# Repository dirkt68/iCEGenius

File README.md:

# iCEGenius (WIP)

**STILL A WORK IN PROGRESS, DONT USE UNTIL THIS MESSAGE IS GONE**

A low cost, low power, minimally sized FPGA development board based on the iCE40LP384 FPGA.

## Table of Contents
- [iCEGenius (WIP)](#icegenius-wip-1)
  - [Table of Contents](#table-of-contents-1)
  - [Project Goal](#project-goal-1)
  - [Setup](#setup-1)
  - [Directory Structure](#directory-structure-1)
  - [Support](#support-1)
  - [Wishlist](#wishlist-1)
  - [Author Information](#author-information-1)

## Project Goal

Hobbyist grade FPGAs are in relatively short supply and are typically complicated for new users to dive into. Even the cheapest ones still range in the 30-40 dollar territory, which can be prohibitively expensive for institutions or groups without a large budget. To fill this void, the iCEGenius has been developed as an educational tool for use in learning introductory to intermediate Verilog on a real hardware target.

{INSERT 3D RENDER PIC}

The iCEGenius has been designed with cost and ease of use in mind. The total bill of materials is only $13.00 USD, which is cheaper than any of the common development FPGAs on the market. The board is designed to fit comfortably into a standard breadboard with space for multiple connections on either pin. With 16 accessible GPIOs, the board is very expandable for anything from simple blinky LEDs to more complex designs.

{INSERT PIC OF BOARD ON BREADBOARD}

The toolchain is a Visual Studio Code extension which supports one click simulations using iverilog and gtkwave and full synthesis using yosys and nextpnr. The [oss-cad-suite](https://github.com/YosysHQ/oss-cad-suite-build) was used as the main backend as all the necessary programs were included by default. A custom program designed to flash the bitstream using the MCP2210 USB-SPI interface is used as the uploader. All of the complicated command line work is handled by the extension, allowing for a low barrier to entry to those who want to learn.

The PCB was developed in Kicad 7.0 and the extension supports Visual Studio Code 1.77.0 and greater.

**IMPORTANT: ONLY WINDOWS IS SUPPORTED AT THIS TIME**

## Setup

1. Grab the latest binary of oss-cad-suite from https://github.com/YosysHQ/oss-cad-suite-build and extract to `C:/oss-cad-suite`.
2. Install the latest binary of the iCEGenius Programmer from the [`Releases`](https://github.com/dirkt68/iCEGenius/releases/) Tab.
3. Install [Visual Studio Code](https://code.visualstudio.com) and install the iCEGenius (ADD HYPERLINK TO EXTENSION) extension.
4. Write some Verilog and upload to your board!

## Directory Structure

- board (where anything related to PCB lives)
  - bom (bill of materials for v2 and v1)
  - iCEGenius-backups (kicad automatic backups)
  - information (datasheets and a pinout guide for the FPGA)
  - jlcpcb (where the production files are autogenerated (gerbers, cpl, etc.))
  - pdf (easy reference to schematic and layout)
  - sims (electronic simulations)
  - kicad board files (open in kicad)
- extension (where the vscode extension lives)
  - standard Visual Studio Code layout for an extension
- programmer (where the program to program the board lives)
  - etc (user guides, etc.)
  - includes (*.h files)
  - libs (*.lib files)
  - src (main code)

## Support
- Any suggestions are welcome! I will not be super active all the time, but I'd like to maintain the project as much as I can.

## Wishlist
- add linux and mac support
- host a prebuilt board somewhere where people can buy (where?)

## Author Information
- Made by Dirk Thieme for use in ECE 2372 for the Capstone Project Lab at Texas Tech University. Advised by Derek A. Johnston.

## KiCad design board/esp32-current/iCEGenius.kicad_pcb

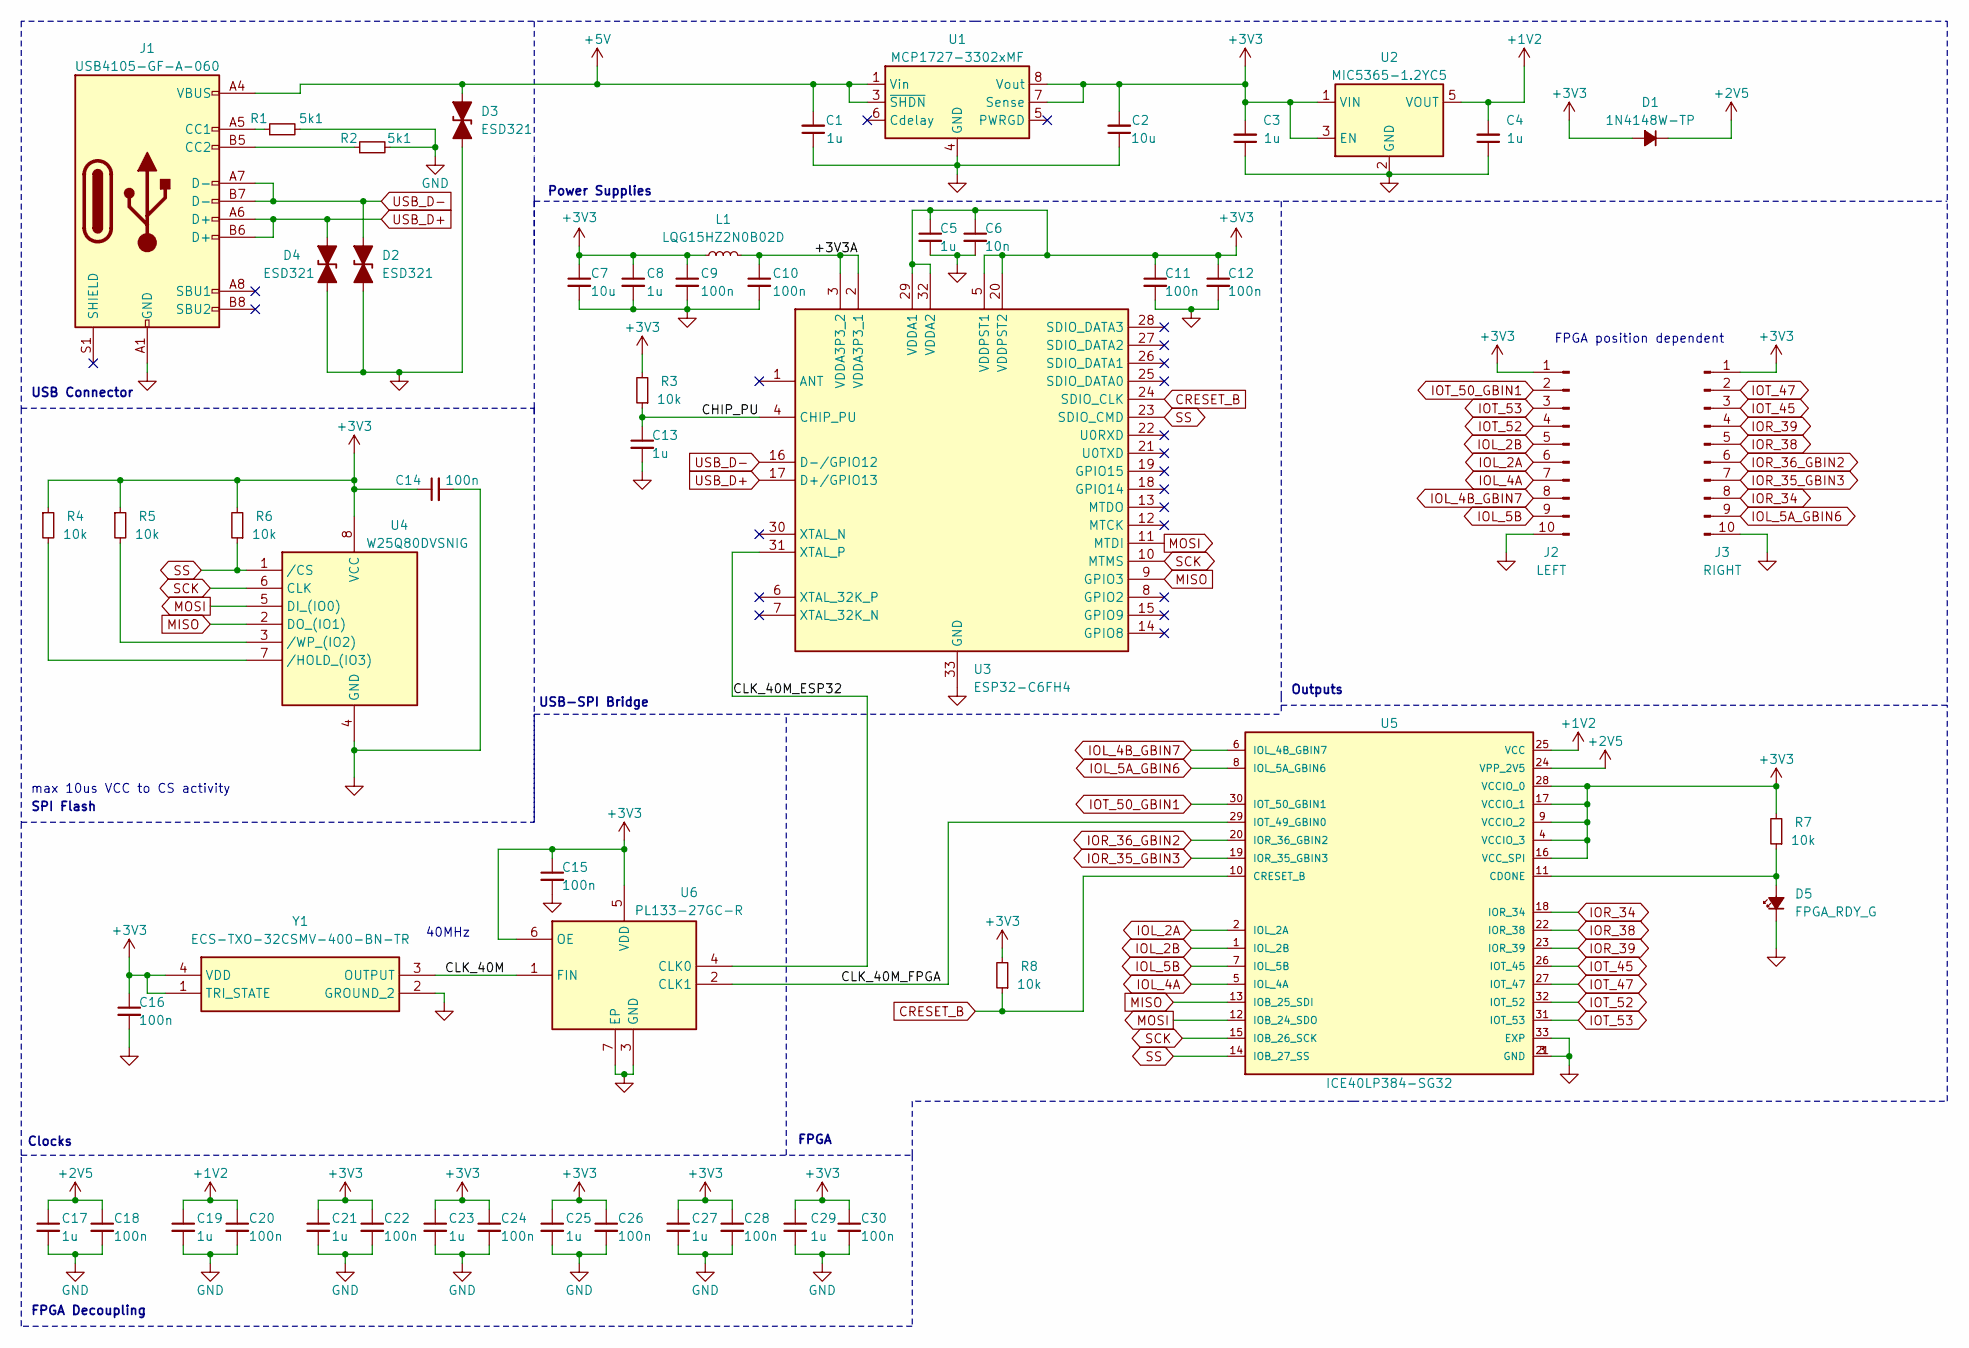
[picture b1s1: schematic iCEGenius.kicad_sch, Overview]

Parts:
C1, C3, C4, C5, C8, C13, C17, C19, C21, C23, C25, C27, C29: 1u; C_0402_1005Metric
C2, C7: 10u; C_0402_1005Metric
C6: 10n; C_0201_0603Metric
C9, C10, C11, C12, C14, C15, C16, C18, C20, C22, C24, C26, C28, C30: 100n; C_0201_0603Metric
D1: 1N4148W-TP; D_SOD-123
D2, D3, D4: ESD321; D_0402_1005Metric_TVS
D5: FPGA_RDY_G; LED_0603_1608Metric
J1: USB4105-GF-A-060; USB_C_Receptacle_GCT_USB4105-xx-A_16P_TopMnt_Horizontal
J2: LEFT; PinSocket_1x10_P2.54mm_Vertical
J3: RIGHT; PinSocket_1x10_P2.54mm_Vertical
L1: LQG15HZ2N0B02D; L_0402_1005Metric
R1, R2: 5k1; R_0402_1005Metric
R3, R4, R5, R6, R7, R8: 10k; R_0402_1005Metric
U1: MCP1727-3302xMF; DFN-8-1EP_3x3mm_P0.65mm_EP1.55x2.4mm
U2: MIC5365-1.2YC5; SOT-353_SC-70-5
U3: ESP32-C6FH4; QFN50P500X500X90-33N; Mouser Part Number 356-ESP32-C6FH4
U4: W25Q80DVSNIG; SOIC127P600X175-8N; Mouser Part Number 454-W25Q80DVSNIG
U5: ICE40LP384-SG32; HVQFN-32-1EP_5x5mm_P0.5mm_EP3.1x3.1mm
U6: PL133-27GC-R; SON40P200X130X60-7N-D; Mouser Part Number 998-PL133-27GC-R
Y1: ECS-TXO-32CSMV-400-BN-TR; ECSTXO32CSMV400BNTR; Mouser Part Number 520-TXO32CSMV400BNTR

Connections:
+1V2: C4.2, C19.1, C20.1, U2.5 (VOUT), U5.25 (VCC)
+2V5: C17.1, C18.1, D1.1 (K), U5.24 (VPP_2V5)
+3V3: C2.2, C3.2, C5.1, C6.1, C7.1, C8.1, C9.1, C11.1, C12.1, C14.1, C15.1, C16.1, C21.1, C22.1, C23.1, C24.1, C25.1, C26.1, C27.1, C28.1, C29.1, C30.1, D1.2 (A), J2.1, J3.1, L1.1, R3.2, R4.1, R5.1, R6.2, R7.2, R8.2, U1.7 (Sense), U1.8 (Vout), U2.1 (VIN), U2.3 (EN), U3.5 (VDDPST1), U3.20 (VDDPST2), U3.29 (VDDA1), U3.32 (VDDA2), U4.8 (VCC), U5.4 (VCCIO_3), U5.9 (VCCIO_2), U5.16 (VCC_SPI), U5.17 (VCCIO_1), U5.28 (VCCIO_0), U6.5 (VDD), U6.6 (OE), Y1.1 (TRI_STATE), Y1.4 (VDD)
+5V: C1.2, D3.2 (A2), J1.A4 (VBUS), J1.A9 (VBUS), J1.B4 (VBUS), J1.B9 (VBUS), U1.1 (Vin), U1.2 (Vin), U1.3 (~SHDN)
/+3V3A: C10.1, L1.2, U3.2 (VDDA3P3_1), U3.3 (VDDA3P3_2)
/CHIP_PU: C13.1, R3.1, U3.4 (CHIP_PU)
/CLK_40M: U6.1 (FIN), Y1.3 (OUTPUT)
/CLK_40M_ESP32: U3.31 (XTAL_P), U6.4 (CLK0)
/CLK_40M_FPGA: U5.29 (IOT_49_GBIN0), U6.2 (CLK1)
CRESET_B: R8.1, U3.24 (SDIO_CLK), U5.10 (CRESET_B)
GND: C1.1, C2.1, C3.1, C4.1, C5.2, C6.2, C7.2, C8.2, C9.2, C10.2, C11.2, C12.2, C13.2, C14.2, C15.2, C16.2, C17.2, C18.2, C19.2, C20.2, C21.2, C22.2, C23.2, C24.2, C25.2, C26.2, C27.2, C28.2, C29.2, C30.2, D2.1 (A1), D3.1 (A1), D4.1 (A1), D5.1 (K), J1.A1 (GND), J1.A12 (GND), J1.B1 (GND), J1.B12 (GND), J2.10, J3.10, R1.2, R2.2, U1.4 (GND), U1.9 (GND), U2.2 (GND), U3.33 (GND), U4.4 (GND), U5.3 (GND), U5.21 (GND), U5.33 (EXP), U6.3 (GND), U6.7 (EP), Y1.2 (GROUND_2)
IOL_2A: J2.6, U5.2 (IOL_2A)
IOL_2B: J2.5, U5.1 (IOL_2B)
IOL_4A: J2.7, U5.5 (IOL_4A)
IOL_4B_GBIN7: J2.8, U5.6 (IOL_4B_GBIN7)
IOL_5A_GBIN6: J3.9, U5.8 (IOL_5A_GBIN6)
IOL_5B: J2.9, U5.7 (IOL_5B)
IOR_34: J3.8, U5.18 (IOR_34)
IOR_35_GBIN3: J3.7, U5.19 (IOR_35_GBIN3)
IOR_36_GBIN2: J3.6, U5.20 (IOR_36_GBIN2)
IOR_38: J3.5, U5.22 (IOR_38)
IOR_39: J3.4, U5.23 (IOR_39)
IOT_45: J3.3, U5.26 (IOT_45)
IOT_47: J3.2, U5.27 (IOT_47)
IOT_50_GBIN1: J2.2, U5.30 (IOT_50_GBIN1)
IOT_52: J2.4, U5.32 (IOT_52)
IOT_53: J2.3, U5.31 (IOT_53)
MISO: U3.9 (GPIO3), U4.2 (DO_(IO1)), U5.13 (IOB_25_SDI)
MOSI: U3.11 (MTDI), U4.5 (DI_(IO0)), U5.12 (IOB_24_SDO)
unnamed: D5.2 (A), R7.1, U5.11 (CDONE)
unnamed: J1.A5 (CC1), R1.1
unnamed: J1.B5 (CC2), R2.1
unnamed: R4.2, U4.7 (/HOLD_(IO3))
unnamed: R5.2, U4.3 (/WP_(IO2))
SCK: U3.10 (MTMS), U4.6 (CLK), U5.15 (IOB_26_SCK)
SS: R6.1, U3.23 (SDIO_CMD), U4.1 (/CS), U5.14 (IOB_27_SS)
USB_D+: D4.2 (A2), J1.A6 (D+), J1.B6 (D+), U3.17 (D+/GPIO13)
USB_D-: D2.2 (A2), J1.A7 (D-), J1.B7 (D-), U3.16 (D-/GPIO12)

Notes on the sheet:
USB-SPI Bridge
SPI Flash
40MHz
Power Supplies
Outputs
max 10us VCC to CS activity
FPGA
Clocks
FPGA position dependent
USB Connector
FPGA Decoupling

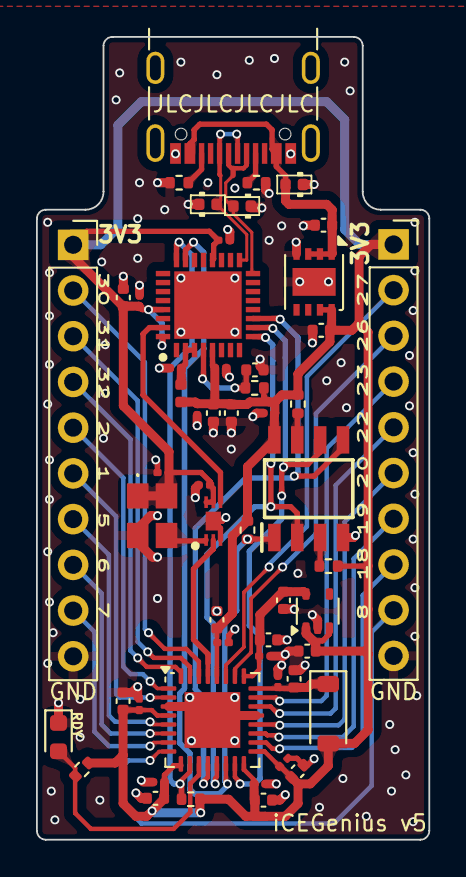
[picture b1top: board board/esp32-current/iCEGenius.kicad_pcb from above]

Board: 4 copper layers, 21.8 x 44.6 mm, 54 parts (0 on the bottom side), 38 nets.

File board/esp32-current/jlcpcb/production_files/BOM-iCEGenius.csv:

Comment,Designator,Footprint,LCSC
1u,C1,C_0402_1005Metric,
100n,C10,C_0201_0603Metric,
100n,C11,C_0201_0603Metric,
100n,C12,C_0201_0603Metric,
1u,C13,C_0402_1005Metric,
100n,C14,C_0201_0603Metric,
100n,C15,C_0201_0603Metric,
100n,C16,C_0201_0603Metric,
1u,C17,C_0402_1005Metric,
100n,C18,C_0201_0603Metric,
1u,C19,C_0402_1005Metric,
10u,C2,C_0402_1005Metric,
100n,C20,C_0201_0603Metric,
1u,C21,C_0402_1005Metric,
100n,C22,C_0201_0603Metric,
1u,C23,C_0402_1005Metric,
100n,C24,C_0201_0603Metric,
1u,C25,C_0402_1005Metric,
100n,C26,C_0201_0603Metric,
1u,C27,C_0402_1005Metric,
100n,C28,C_0201_0603Metric,
1u,C29,C_0402_1005Metric,
1u,C3,C_0402_1005Metric,
100n,C30,C_0201_0603Metric,
1u,C4,C_0402_1005Metric,
1u,C5,C_0402_1005Metric,
10n,C6,C_0201_0603Metric,
10u,C7,C_0402_1005Metric,
1u,C8,C_0402_1005Metric,
100n,C9,C_0201_0603Metric,
1N4148W-TP,D1,D_SOD-123,
ESD321,D2,D_0402_1005Metric_TVS,
ESD321,D3,D_0402_1005Metric_TVS,
ESD321,D4,D_0402_1005Metric_TVS,
FPGA_DONE_G,D5,LED_0603_1608Metric,
USB4105-GF-A-060,J1,USB_C_Receptacle_GCT_USB4105-xx-A_16P_TopMnt_Horizontal,
LEFT,J2,PinSocket_1x10_P2.54mm_Vertical,
RIGHT,J3,PinSocket_1x10_P2.54mm_Vertical,
LQG15HZ2N0B02D,L1,L_0402_1005Metric,
5k1,R1,R_0402_1005Metric,
5k1,R2,R_0402_1005Metric,
10k,R3,R_0402_1005Metric,
10k,R4,R_0402_1005Metric,
10k,R5,R_0402_1005Metric,
10k,R6,R_0402_1005Metric,
10k,R7,R_0402_1005Metric,
10k,R8,R_0402_1005Metric,
MCP1727-3302xMF,U1,DFN-8-1EP_3x3mm_P0.65mm_EP1.55x2.4mm,
MIC5365-1.2YC5,U2,SOT-353_SC-70-5,
ESP32-C6FH4,U3,QFN50P500X500X90-33N,
W25Q80DVSNIG,U4,SOIC127P600X175-8N,
ICE40LP384-SG32,U5,HVQFN-32-1EP_5x5mm_P0.5mm_EP3.1x3.1mm,
PL133-27GC-R,U6,SON40P200X130X60-7N-D,
ECS-TXO-32CSMV-400-BN-TR,Y1,ECSTXO32CSMV400BNTR,

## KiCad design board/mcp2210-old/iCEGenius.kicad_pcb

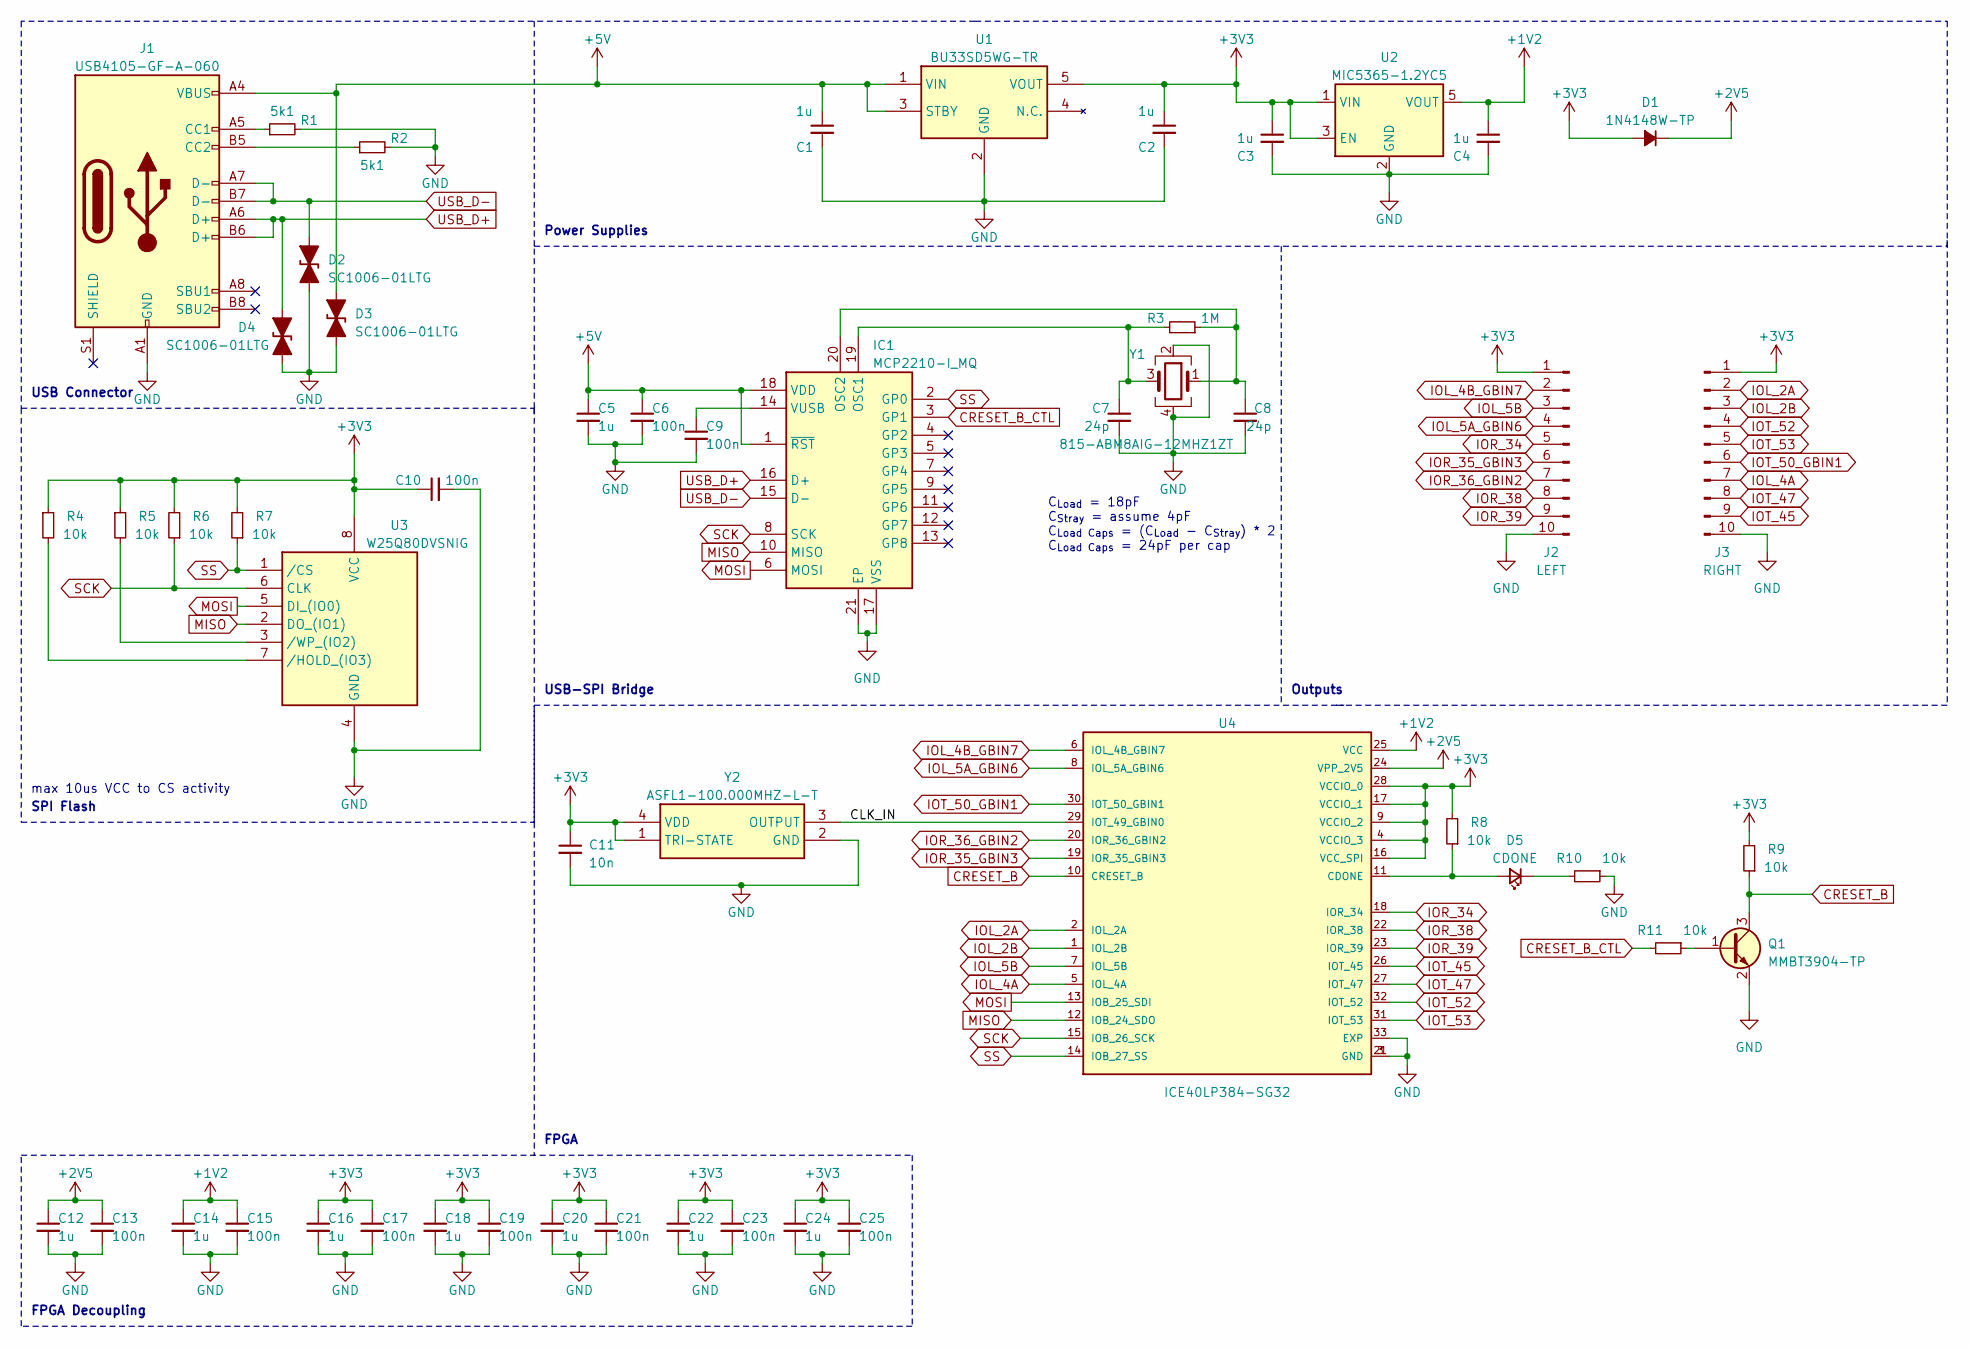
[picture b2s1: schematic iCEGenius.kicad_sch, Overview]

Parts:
C1, C2, C3, C4, C5, C12, C14, C16, C18, C20, C22, C24: 1u; C_0402_1005Metric
C6, C9, C10, C13, C15, C17, C19, C21, C23, C25: 100n; C_0201_0603Metric
C7, C8: 24p; C_0201_0603Metric
C11: 10n; C_0201_0603Metric
D1: 1N4148W-TP; D_SOD-123
D2, D3, D4: SC1006-01LTG; D_SOD-523_TVS
D5: CDONE; D_0603_1608Metric
IC1: MCP2210-I_MQ; QFN65P500X500X100-21N-D; Mouser Part Number 579-MCP2210IMQ
J1: USB4105-GF-A-060; USB_C_Receptacle_GCT_USB4105-xx-A_16P_TopMnt_Horizontal
J2: LEFT; PinSocket_1x10_P2.54mm_Vertical
J3: RIGHT; PinSocket_1x10_P2.54mm_Vertical
Q1: MMBT3904-TP; SOT-23
R1, R2: 5k1; R_0402_1005Metric
R3: 1M; R_0402_1005Metric
R4, R5, R6, R7, R8, R9, R10, R11: 10k; R_0402_1005Metric
U1: BU33SD5WG-TR; SOT95P280X125-5N; Mouser Part Number 755-BU33SD5WG-TR
U2: MIC5365-1.2YC5; SOT-353_SC-70-5
U3: W25Q80DVSNIG; SOIC127P600X175-8N; Mouser Part Number 454-W25Q80DVSNIG
U4: ICE40LP384-SG32; HVQFN-32-1EP_5x5mm_P0.5mm_EP3.1x3.1mm
Y1: 815-ABM8AIG-12MHZ1ZT; ABM8AIG25000MHZ122ZT3
Y2: ASFL1-100.000MHZ-L-T; ASFL1; Manufacturer_Part_Number ASFL1-100.000MHZ-L-T

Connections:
+1V2: C4.1, C14.1, C15.1, U2.5 (VOUT), U4.25 (VCC)
+2V5: C12.1, C13.1, D1.1 (K), U4.24 (VPP_2V5)
+3V3: C2.1, C3.1, C10.1, C11.1, C16.1, C17.1, C18.1, C19.1, C20.1, C21.1, C22.1, C23.1, C24.1, C25.1, D1.2 (A), J2.1, J3.1, R4.1, R5.1, R6.2, R7.2, R8.2, R9.2, U1.5 (VOUT), U2.1 (VIN), U2.3 (EN), U3.8 (VCC), U4.4 (VCCIO_3), U4.9 (VCCIO_2), U4.16 (VCC_SPI), U4.17 (VCCIO_1), U4.28 (VCCIO_0), Y2.1 (TRI-STATE), Y2.4 (VDD)
+5V: C1.1, C5.1, C6.1, D3.2 (A2), IC1.1 (~RST), IC1.18 (VDD), J1.A4 (VBUS), J1.A9 (VBUS), J1.B4 (VBUS), J1.B9 (VBUS), U1.1 (VIN), U1.3 (STBY)
/CLK_IN: U4.29 (IOT_49_GBIN0), Y2.3 (OUTPUT)
CRESET_B: Q1.3 (C), R9.1, U4.10 (CRESET_B)
CRESET_B_CTL: IC1.3 (GP1), R11.2
GND: C1.2, C2.2, C3.2, C4.2, C5.2, C6.2, C7.2, C8.2, C9.2, C10.2, C11.2, C12.2, C13.2, C14.2, C15.2, C16.2, C17.2, C18.2, C19.2, C20.2, C21.2, C22.2, C23.2, C24.2, C25.2, D2.1 (A1), D3.1 (A1), D4.1 (A1), IC1.17 (VSS), IC1.21 (EP), J1.A1 (GND), J1.A12 (GND), J1.B1 (GND), J1.B12 (GND), J2.10, J3.10, Q1.2 (E), R1.2, R2.2, R10.1, U1.2 (GND), U2.2 (GND), U3.4 (GND), U4.3 (GND), U4.21 (GND), U4.33 (EXP), Y1.2, Y1.4, Y2.2 (GND)
IOL_2A: J3.2, U4.2 (IOL_2A)
IOL_2B: J3.3, U4.1 (IOL_2B)
IOL_4A: J3.7, U4.5 (IOL_4A)
IOL_4B_GBIN7: J2.2, U4.6 (IOL_4B_GBIN7)
IOL_5A_GBIN6: J2.4, U4.8 (IOL_5A_GBIN6)
IOL_5B: J2.3, U4.7 (IOL_5B)
IOR_34: J2.5, U4.18 (IOR_34)
IOR_35_GBIN3: J2.6, U4.19 (IOR_35_GBIN3)
IOR_36_GBIN2: J2.7, U4.20 (IOR_36_GBIN2)
IOR_38: J2.8, U4.22 (IOR_38)
IOR_39: J2.9, U4.23 (IOR_39)
IOT_45: J3.9, U4.26 (IOT_45)
IOT_47: J3.8, U4.27 (IOT_47)
IOT_50_GBIN1: J3.6, U4.30 (IOT_50_GBIN1)
IOT_52: J3.4, U4.32 (IOT_52)
IOT_53: J3.5, U4.31 (IOT_53)
MISO: IC1.10 (MISO), U3.2 (DO_(IO1)), U4.12 (IOB_24_SDO)
MOSI: IC1.6 (MOSI), U3.5 (DI_(IO0)), U4.13 (IOB_25_SDI)
unnamed: D5.2 (A), R8.1, U4.11 (CDONE)
unnamed: D5.1 (K), R10.2
unnamed: C7.1, IC1.19 (OSC1), R3.2, Y1.3
unnamed: C8.1, IC1.20 (OSC2), R3.1, Y1.1
unnamed: C9.1, IC1.14 (VUSB)
unnamed: J1.A5 (CC1), R1.1
unnamed: J1.B5 (CC2), R2.1
unnamed: Q1.1 (B), R11.1
unnamed: R4.2, U3.7 (/HOLD_(IO3))
unnamed: R5.2, U3.3 (/WP_(IO2))
SCK: IC1.8 (SCK), R6.1, U3.6 (CLK), U4.15 (IOB_26_SCK)
SS: IC1.2 (GP0), R7.1, U3.1 (/CS), U4.14 (IOB_27_SS)
USB_D+: D4.2 (A2), IC1.16 (D+), J1.A6 (D+), J1.B6 (D+)
USB_D-: D2.2 (A2), IC1.15 (D-), J1.A7 (D-), J1.B7 (D-)

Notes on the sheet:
USB-SPI Bridge
SPI Flash
Power Supplies
Outputs
max 10us VCC to CS activity
C_{Load} = 18pF C_{Stray} = assume 4pF C_{Load Caps} = (C_{Load} - C_{Stray}) * 2 C_{Load Caps} = 24pF per cap
FPGA
USB Connector
FPGA Decoupling

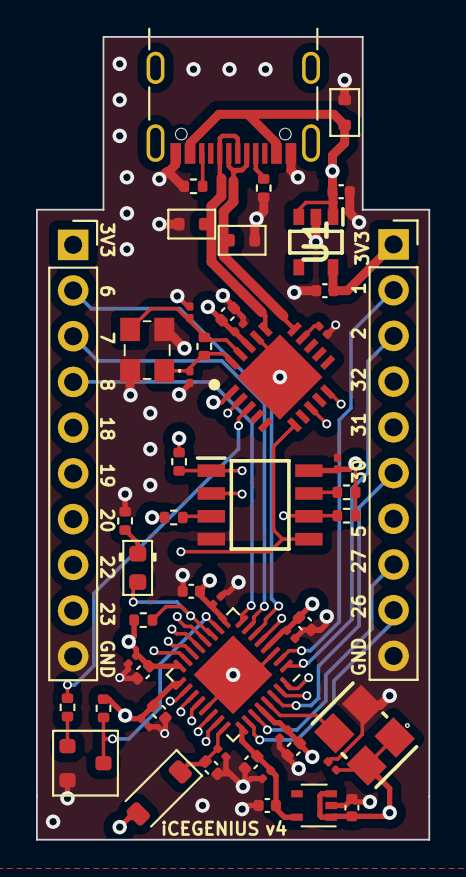
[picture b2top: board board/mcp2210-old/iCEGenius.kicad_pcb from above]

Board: 6 copper layers, 21.8 x 44.6 mm, 52 parts (0 on the bottom side), 40 nets.

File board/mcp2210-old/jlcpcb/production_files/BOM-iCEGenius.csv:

Comment,Designator,Footprint,LCSC
10k,R8,R_0402_1005Metric,
815-ABM8AIG-12MHZ1ZT,Y1,ABM8AIG25000MHZ122ZT3,
10n,C11,C_0201_0603Metric,
1M,R3,R_0402_1005Metric,
1u,C12,C_0402_1005Metric,
100n,C21,C_0201_0603Metric,
1u,C20,C_0402_1005Metric,
100n,C9,C_0201_0603Metric,
"MMBT3904-TP
",Q1,SOT-23,
10k,R10,R_0402_1005Metric,
CDONE,D5,D_0603_1608Metric,
ASFL1-100.000MHZ-L-T,Y2,ASFL1,
W25Q80DVSNIG,U3,SOIC127P600X175-8N,
MIC5365-1.2YC5,U2,SOT-353_SC-70-5,
BU33SD5WG-TR,U1,SOT95P280X125-5N,
10k,R11,R_0402_1005Metric,
10k,R9,R_0402_1005Metric,
10k,R7,R_0402_1005Metric,
10k,R6,R_0402_1005Metric,
10k,R5,R_0402_1005Metric,
10k,R4,R_0402_1005Metric,
5k1,R2,R_0402_1005Metric,
5k1,R1,R_0402_1005Metric,
USB4105-GF-A-060,J1,USB_C_Receptacle_GCT_USB4105-xx-A_16P_TopMnt_Horizontal,
MCP2210-I_MQ,IC1,QFN65P500X500X100-21N-D,
SC1006-01LTG,D4,D_SOD-523_TVS,
SC1006-01LTG,D3,D_SOD-523_TVS,
SC1006-01LTG,D2,D_SOD-523_TVS,
1N4148W-TP,D1,D_SOD-123,
100n,C25,C_0201_0603Metric,
1u,C24,C_0402_1005Metric,
100n,C23,C_0201_0603Metric,
1u,C22,C_0402_1005Metric,
100n,C19,C_0201_0603Metric,
1u,C18,C_0402_1005Metric,
100n,C17,C_0201_0603Metric,
1u,C16,C_0402_1005Metric,
100n,C15,C_0201_0603Metric,
1u,C14,C_0402_1005Metric,
100n,C13,C_0201_0603Metric,
100n,C10,C_0201_0603Metric,
24p,C8,C_0201_0603Metric,
24p,C7,C_0201_0603Metric,
100n,C6,C_0201_0603Metric,
1u,C5,C_0402_1005Metric,
1u,C4,C_0402_1005Metric,
1u,C3,C_0402_1005Metric,
1u,C2,C_0402_1005Metric,
1u,C1,C_0402_1005Metric,
RIGHT,J3,PinSocket_1x10_P2.54mm_Vertical,
LEFT,J2,PinSocket_1x10_P2.54mm_Vertical,
ICE40LP384-SG32,U4,HVQFN-32-1EP_5x5mm_P0.5mm_EP3.1x3.1mm,

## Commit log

2023-04-20 First push
2023-06-02 updated board to v2, setup vscode extension
2023-06-02 recommited new board files
2023-06-03 README update, deleted old files
2023-06-07 Added software-flowcharts
2023-06-07 Update software-flowcharts
2023-06-10 vscode extension progress
2023-06-14 finsihed simulation part of vscode extensions
2023-06-14 minor change in path detection
2023-06-14 added .gitignore for stuff
2023-06-14 tweaked README
2023-06-14 tweaked README again
2023-06-14 Create LICENSE
2023-06-14 changed LICENSE
2023-06-14 another edit
2023-07-10 linux push
2023-07-11 updated code and mostly finished extension
2023-08-31 uploaded current state - unfinished
2024-08-26 finished v5 of PCB in ESP32 folder
2024-08-26 created esp-fpgaloader program folder
2024-08-28 updated extension to automatically install required programs on Windows, macos, and Linux
2026-02-07 cleanup README
